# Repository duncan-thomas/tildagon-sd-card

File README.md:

An SD card hexpansion board for the EMF24 Tildagon badge.

Uses the cheap SD breakout boards rather than me trying to solder the socket.

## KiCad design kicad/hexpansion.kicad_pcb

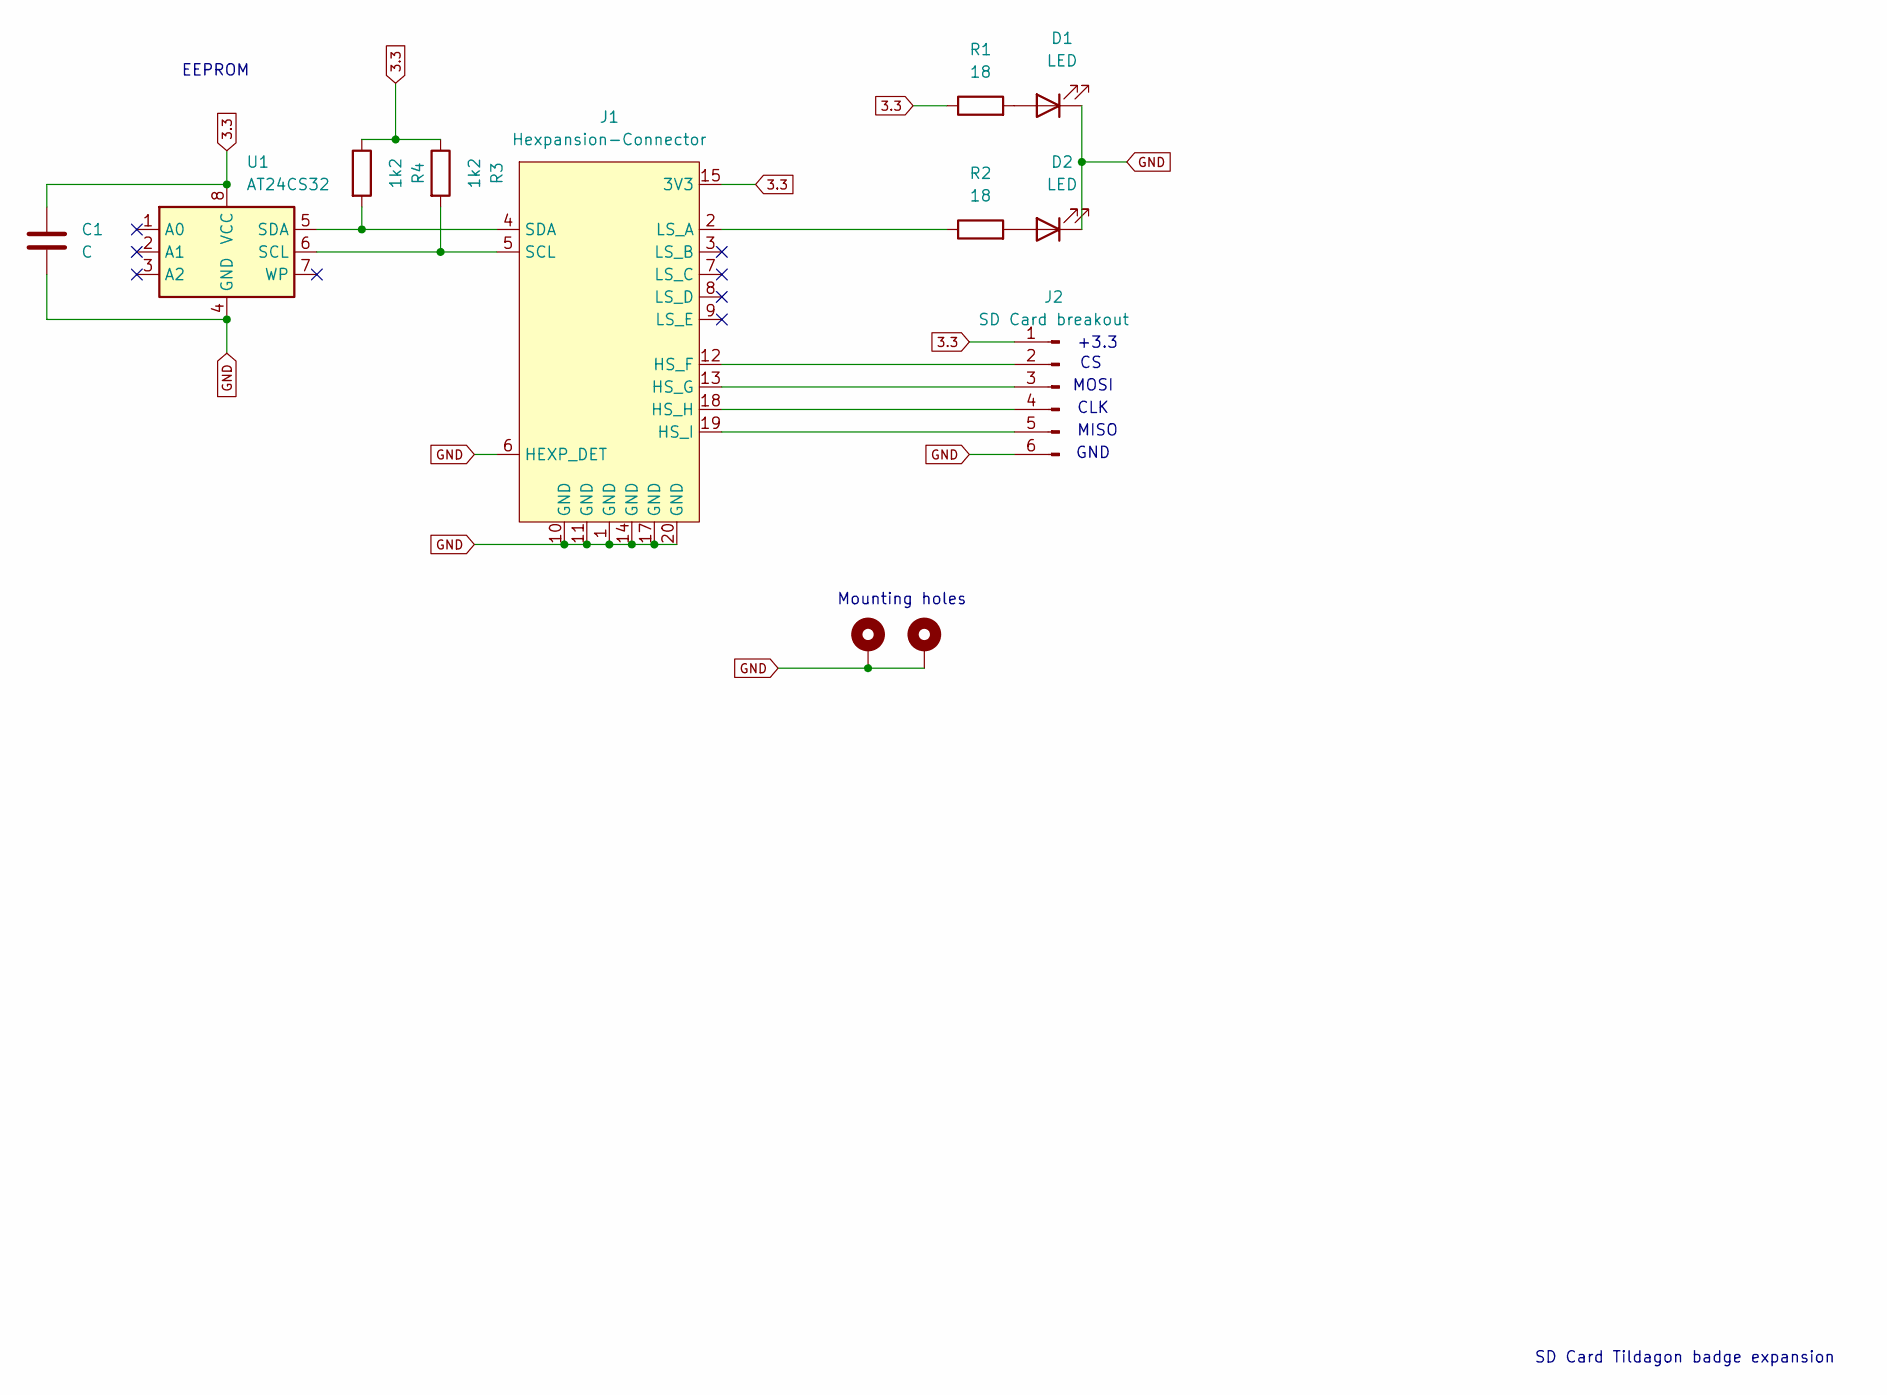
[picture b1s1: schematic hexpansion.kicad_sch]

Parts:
C1: C; C_0603_1608Metric_Pad1.08x0.95mm_HandSolder
D1, D2: LED; LED_0805_2012Metric
H1, H2: MountingHole_Pad; MountingHole_2.2mm_M2_Pad_Via
J1: Hexpansion-Connector; hexpansion-edge-connector
J2: SD Card breakout; PinHeader_1x06_P2.54mm_Vertical
R1, R2: 18; R_0603_1608Metric
R3, R4: 1k2; R_0603_1608Metric
U1: AT24CS32; SOIC-8_3.9x4.9mm_P1.27mm

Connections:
3.3: C1.2, J1.15 (3V3), J1.16 (3V3), J2.1, R1.1, R3.1, R4.1, U1.8 (VCC)
GND: C1.1, D1.1 (K), D2.1 (K), H1.1, H2.1, J1.1 (GND), J1.6 (HEXP_DET), J1.10 (GND), J1.11 (GND), J1.14 (GND), J1.17 (GND), J1.20 (GND), J2.6, U1.4 (GND)
unnamed: D1.2 (A), R1.2
unnamed: D2.2 (A), R2.2
unnamed: J1.12 (HS_F), J2.2
unnamed: J1.13 (HS_G), J2.3
unnamed: J1.18 (HS_H), J2.4
unnamed: J1.19 (HS_I), J2.5
unnamed: J1.2 (LS_A), R2.1
unnamed: J1.5 (SCL), R3.2, U1.6 (SCL)
unnamed: J1.4 (SDA), R4.2, U1.5 (SDA)

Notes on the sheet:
+3.3
SD Card Tildagon badge expansion
CLK
EEPROM
GND
MISO
Mounting holes
MOSI

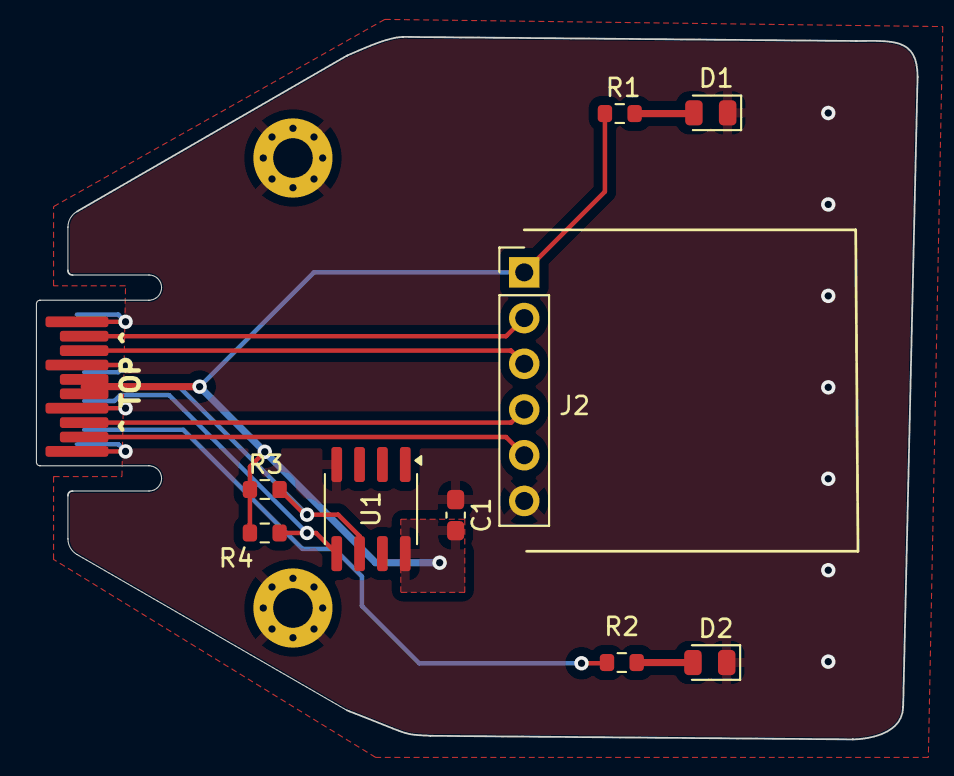
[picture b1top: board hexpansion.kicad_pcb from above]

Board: 2 copper layers, 48.9 x 39.0 mm, 12 parts (0 on the bottom side), 11 nets.

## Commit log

2025-06-02 Initial attempt
    Based on what I cobbled together with a breadboard.
    PCB has had no optimisation done to it at all yet.
2025-06-03 Remove footprint cache
    This is regenerated automatically. We add it to .gitignore so that it
    can sit around doing its job without causing issues
2025-06-03 Add Makefile to render board
    Generate schematic pdf, board pdf, and a board 3d render STEP file.
2025-06-03 Simplify
    Based on the guidelines on r/PrintedCircuitBoards I'd removed most of the
    use of nets in the schematic, and added ground fills on the PCB
2025-06-03 Add decoupling cap
    Not yet sure if I'll need it, but definitely no harm in leaving room for
    a decoupling cap for the flash chip.
    The SD card breakout boards already have them built in.
2025-06-03 Ignore kicad lock files
    They aren't something we want adding to git by accident
2025-06-03 Reorder GPIOs to simplify layout
    Reordering the highspeed GPIOs made the SPI routing dead simple.
    Reworked the rest of the board around that.
2025-06-03 Tweak capacitor placement
    Give the flash chip a touch more breathing room
2025-06-03 Minor tweaks
    * Move track away from mounting hole
    * Tweak outline to fit within the limits - it was bulging over
    fractionally
2025-06-03 Fill all fills
    Forgot to re-run the fill after the latest changes
2025-06-03 More tweaks
    * Increased the gab between a track and a via since it was generating a
    warning
    * Set up some design rules to match JLC PCB
    * Adding the JLC PCB fabrication manager
